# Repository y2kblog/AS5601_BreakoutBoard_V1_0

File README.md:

# 12bit (4096P/R) 磁気式エンコーダAS5601 Breakout Board

[English page](https://products.y2kb.com/en/as5601/latest/)

## 概要

12bit (4096P/R) 分解能の磁気式アブソリュートエンコーダ AS5601 (ams AG製) を2.54mmピッチに変換する基板です。ネオジム磁石を同梱。  
5V、3.3V、GNDの電源ピンとI2C、A/B相インクリメンタル出力のピンが出ています。電源電圧は5Vもしくは3.3Vです。  
**※AS5600との違いはAS5600の出力方式がアナログ/PWM出力であるのに対し、AS5601はA/B相のインクリメンタル出力である点です。**

### AS5601の特徴
- 4096P/R の高分解能 (インクリメンタル出力は最大2048ppr)
- 磁気式のため非接触で角度計測が可能であり、信頼性と耐久性に優れている
- インターフェイス：I2C、インクリメンタル出力、PUSHピン
- I2C：設定レジスタにアクセスでき、角度の読み取りや動作設定が可能
- インクリメンタル出力：8ppr～2048pprの分解能設定が可能なA/B相の直交出力
- サンプリング時間：150μs
- AS5601とネオジム磁石の軸中心が1mm程度ずれても値の読み取りが可能

### 基板仕様
- 基板サイズ：横20mm×縦13.5ｍｍ
- 基板マウント用穴：15mmピッチ、M3×2穴
- 電源電圧に5Vを供給する場合は3.3Vピンをオープンに、3.3Vを供給する場合は5Vピンにも3.3Vを供給してください。
- PUSHピンは接続されていないためアクセスできません

## 販売  
[スイッチサイエンス委託販売ページ](https://www.switch-science.com/catalog/3494/)  
※大量注文や在庫に関する問い合わせは[こちら](mailto:info.y2kb@gmail.com)までご連絡ください。  

## 内容物
- AS5601 Breakout Board 本体
- エンコーダ用ネオジム磁石

### 回路図  

### 寸法  

## 取付方法
1. 同梱のネオジム磁石を回転体の軸中心に取り付けます
2. AS5601の中心とネオジム磁石の中心が合うよう基板を固定部に取り付けます

**取付例**  

## Arduinoによるプログラム例  

### I2Cによる角度の取得  
#### 配線図  

#### [ソースファイル](https://github.com/y2kblog/AS5601_BreakoutBoard_V1_0/blob/master/SampleCode/Arduino/I2C_SampleCode/I2C_SampleCode.ino)

<!--
#### ソースファイルのディレクトリ  
"SampleCode/Arduino/I2C_SampleCode/I2C_SampleCode.ino"
-->

#### ミニマムコード  

```cpp
#include <stdint.h>
#include <Wire.h>
#define AS5600_AS5601_DEV_ADDRESS      0x36
#define AS5600_AS5601_REG_RAW_ANGLE    0x0C

void setup() {
  // I2C init
  Wire.begin();
  Wire.setClock(400000);

  // Read RAW_ANGLE value from encoder
  Wire.beginTransmission(AS5600_AS5601_DEV_ADDRESS);
  Wire.write(AS5600_AS5601_REG_RAW_ANGLE);
  Wire.endTransmission(false);
  Wire.requestFrom(AS5600_AS5601_DEV_ADDRESS, 2);
  uint16_t RawAngle = 0;
  RawAngle  = ((uint16_t)Wire.read() << 8) & 0x0F00;
  RawAngle |= (uint16_t)Wire.read();
  // Raw angle value (0 ~ 4095) is stored in RawAngle
}

void loop() {
}
```

### インクリメンタル出力ピンを用いた角度の取得  
#### 配線図  

#### [ソースファイル](https://github.com/y2kblog/AS5601_BreakoutBoard_V1_0/blob/master/SampleCode/Arduino/Incremental_SampleCode/Incremental_SampleCode.ino)

<!--
#### ソースファイルのディレクトリ  
"SampleCode/Arduino/Incremental_SampleCode/Incremental_SampleCode.ino"
-->

#### ミニマムコード
```cpp
#include <stdint.h>
#include <Wire.h>
#define AS5600_AS5601_DEV_ADDRESS       0x36
#define AS5601_REG_ABN                  0x09

volatile int32_t EncoderCount;

void Encoder_GPIO_init(void) {
  DDRD  &= ~((1 << PD2) | (1 << PD3));  // Set PD2 and PD3 as input
  EICRA = 0b00000101; // Trigger event of INT0 and INT1 : Any Logic Change
  EIMSK = 0b00000011; // Enable interrupt INT0 and INT1
  sei();              //Enable Global Interrupt
}

// Encoder "A" pin logic change interrupt callback function
ISR(INT0_vect) {
  updateEncoderCount();
}

// Encoder "B" pin logic change interrupt callback function
ISR(INT1_vect) {
  updateEncoderCount();
}

void updateEncoderCount(void) {
  const static int8_t EncoderIndexTable[] =
    {0, -1, 1, 0,  1, 0, 0, -1,  -1, 0, 0, 1,  0, 1, -1, 0};
  static uint8_t EncoderPinState_Now, EncoderPinState_Prev = 0;

  EncoderPinState_Now = (PIND >> 2) & 0x03; // Bit1 : PD3 (Encoder B), Bit0 : PD2 (Encoder A)
  EncoderCount += EncoderIndexTable[EncoderPinState_Prev << 2 | EncoderPinState_Now];
  EncoderPinState_Prev = EncoderPinState_Now;
}

void Encoder_I2C_init(void) {
  // Set AS5601 resolution 2048ppr
  Wire.beginTransmission(AS5600_AS5601_DEV_ADDRESS);
  Wire.write(AS5601_REG_ABN);
  Wire.write(0b00001000);   // ABN(3:0)
  Wire.endTransmission();
  delay(1);
}

void setup() {
  // I2C init
  Wire.begin();
  Wire.setClock(400000);

  // Peripheral init
  Encoder_I2C_init();
  Encoder_GPIO_init();
}

void loop() {
  // Angle value (0 ~ 2047) is stored in EncoderCount
}
```

<!--
#### HAL (STM32)

**サンプルコード**

    // I2Cの初期化は終わっているとする

    #define AS5600_AS5601_DEV_ADDRESS      (0x36<<1)
    #define AS5600_AS5601_REG_RAW_ANGLE    0x0C

    uint8_t buf[2];
    HAL_I2C_Mem_Read(&hi2c, AS5600_AS5601_DEV_ADDRESS,
      AS5600_AS5601_REG_RAW_ANGLE, I2C_MEMADD_SIZE_8BIT,
      (uint8_t*)buf, 2, 1000);
    uint16_t RawAngle;
    RawAngle = (uint16_t) buf[0] << 8 | (uint16_t) buf[1];
    RawAngle &= 0x0FFF;
    // Raw angle value (0x0000~0x0FFF) is stored in RawAngle

### コンフィグのメモリへの焼き付け  

-->

### 設定レジスタの焼き付けによる分解能の固定

AS5601のデフォルトの分解能は8pprなので、初期状態ですと電源投入毎に分解能を設定する必要があります。
そこで、分解能を2048pprに設定後にBurn_Settingコマンドにより設定レジスタを焼くことで、電源を落として再度電源を投入しても起動時から2048pprに設定された状態で固定され、I2Cにより分解能等の設定情報を再設定する必要がなくなります。  
**※一度書き込むと以後分解能やフィルタ設定などを変更することはできなくなります。**

サンプルコードは[こちら](https://github.com/y2kblog/AS5601_BreakoutBoard_V1_0/blob/master/SampleCode/Arduino/burnConfig_SampleCode/burnConfig_SampleCode.ino)。

## 資料

- 2Dデータ(DXF)：<a href="https://github.com/y2kblog/AS5601_BreakoutBoard_V1_0/raw/master/PCB_source/dxf/AS5601_BreakoutBoard_V1_0_dxf.zip" download="">AS5601_BreakoutBoard_V1_0_dxf.zip</a>  
- 3Dデータ(STEP)：<a href="https://github.com/y2kblog/AS5601_BreakoutBoard_V1_0/raw/master/PCB_source/step/AS5601_BreakoutBoard_V1_0_step.zip" download="">AS5601_BreakoutBoard_V1_0_step.zip</a>  

## License
MIT License

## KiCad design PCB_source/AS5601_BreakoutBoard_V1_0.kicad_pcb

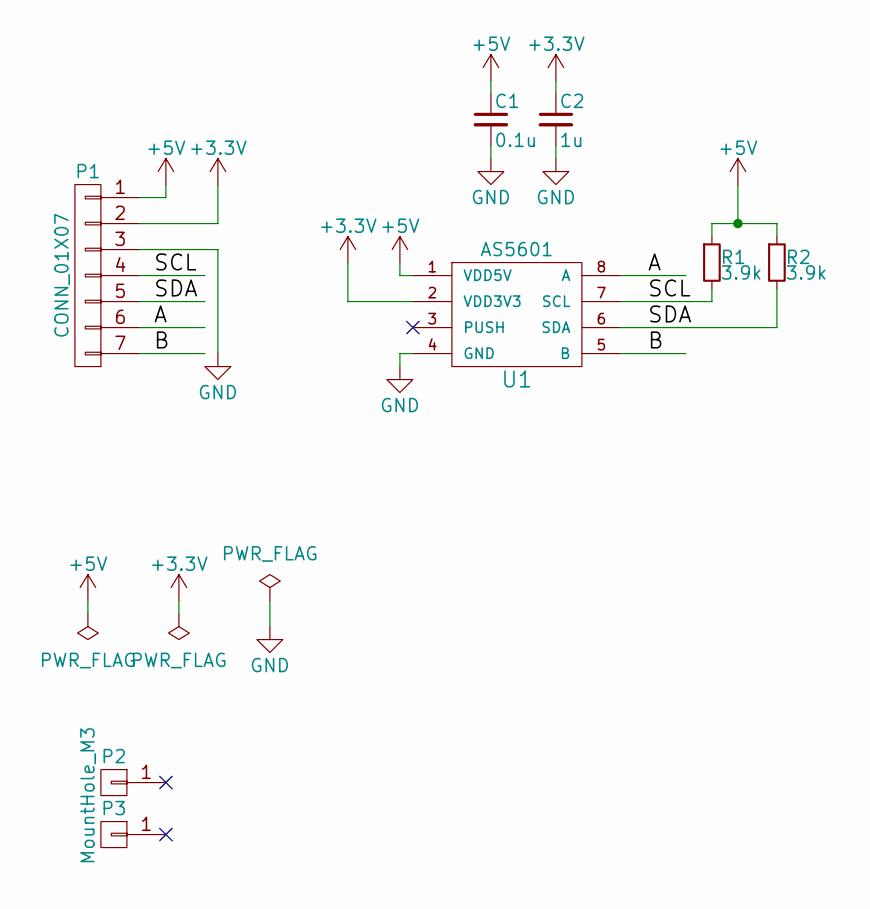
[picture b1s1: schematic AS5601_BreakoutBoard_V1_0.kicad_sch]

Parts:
C1: 0.1u; C_0603_HandSoldering
C2: 1u; C_0603_HandSoldering
P1: CONN_01X07; USER_SIL-7
P2, P3: MountHole_M3; MountingHole_3.2mm_M3
R1, R2: 3.9k; R_0603_HandSoldering
U1: AS5601; SOIC-8_3.9x4.9mm_Pitch1.27mm

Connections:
+3V3: C2.1, P1.2, U1.2 (VDD3V3)
+5V: C1.1, P1.1, R1.1, R2.1, U1.1 (VDD5V)
/A: P1.6, U1.8 (A)
/B: P1.7, U1.5 (B)
/SCL: P1.4, R1.2, U1.7 (SCL)
/SDA: P1.5, R2.2, U1.6 (SDA)
GND: C1.2, C2.2, P1.3, U1.4 (GND)

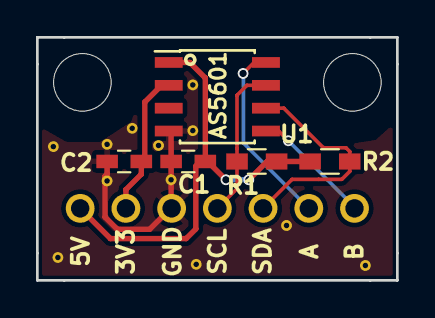
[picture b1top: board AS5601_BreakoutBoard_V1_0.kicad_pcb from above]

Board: 2 copper layers, 20.0 x 13.5 mm, 19 parts (1 on the bottom side), 7 nets.

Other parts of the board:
11, 12, 21, 22, 31, 32, 41, 41#2, 42, 51, 52: USER_GNDvia

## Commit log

2017-09-03 :confetti_ball: Added .gitattributes & .gitignore files
2017-09-03 init
2017-09-07 fix sample code bug
2017-09-17 Add sample code using Incremental output
2017-09-21 Add minimum code
2017-09-22 Add circuit diagram
2018-05-28 Add burnConfig sample code
2018-12-23 add burnConfig
2021-09-18 add step and refactoring
2021-09-18 add syntax highlighting
2021-09-23 add DXF
2022-12-07 add link
2023-02-09 kicad v6
